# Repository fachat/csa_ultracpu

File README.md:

# Ultra-CPU

Note: this is a part of a larger set of repositories, with [upet_family](https://github.com/fachat/upet_family) as the main repository.

This is the CPU board for a re-incarnation of the Commodore PET or other computer(s) from the later 1970s.

It is build on a Eurocard board and has only parts that can still be obtained new in 2024.
It uses the [CS/A bus interface](http://www.6502.org/users/andre/csa/index.html) to use other I/O boards.

As the memory mapping is programmable using the FPGA on the board, multiple types of computers can
potentially re-created. I started with my favourite one, the Commodore PET.

The reason this board is called Ultra-CPU is because it can potentially be used to recreate not only the Commodore PET.
The downside compared to the Micro-PET is, that it needs a separate I/O board to re-create a Commodore PET.
This can be found [here on my CS/A page](http://www.6502.org/users/andre/csa/petio/index.html).

## Features

The board is built with a number of features:

- Commodore 3032 / 4032 / 8032 / 8296 with options menu to select at boot
  - Boot-menu to select different PET versions to run (BASIC 1, 2, 4)
  - 40 col character display
  - 80 col character display
- Improved system design:
  - 512k video RAM, plus 512k fast RAM, accessible using banks on the W65816 CPU
  - boot from an SPI Flash ROM
  - up to 17.5 MHz mode (via configuration register)
  - Write protection for the PET ROMs once copied to RAM
  - lower 32k RAM mappable from all of the 512k fast RAM
- Improved Video output:
  - VGA color video output (RGBI in 768x576 mode)
  - based on 720x576@60Hz VGA video timing (i.e. including borders at 40/80 columns)
  - modifyable character set
  - 40/80 column display switchable
  - 25/50 rows display switch
  - multiple video pages mappable to $8000 video mem address
  - Mulitple colour modes (Colour-PET, C128 VDC-compatible, Multicolour)
  - Colour Hires (VDC-compatible, Multicolour)
  - 16 colours out of a colour palette of 64 colours displayed simultaneously.
- DAC audio output
  - DMA engine to play audio samples on stereo sound output
- Built-in extra hardware:
  - USB host mode interface (for keyboard / mouse)
  - Real-Time-Clock (battery-buffered)
  - Ethernet/Wifi (via Breakout board)
  - SD-Card (via Breakout board)
- CS/A bus interface
  - multiple options to use bus devices, e.g. in I/O window
  - Together with [Ultra-Bus](https://github.com/fachat/csa_ultrabus) backplane Apple-II and RC2014 devices can be used

## Overview

The system architecture is actually rather simple, as you can see in the following graphics.

The main functionality is "hidden" inside the FPGA. It does:

1. clock generation and management
2. memory mapping
3. video generation.
4. SPI interface and boot

On the CPU side of the FPGA it is actually a rather almost normal 65816 computer, 
with the exception that the bank register (that catches and stores the address lines 
A16-23 from the CPU's data bus) is in the FPGA, and that there is no ROM. The ROM has been
replaced with some code in the FPGA that copies the initial program to the CPU accessible
RAM, taking it from the Flash Boot ROM via SPI. This actually simplifies the design,
as 

1. parallel ROMs are getting harder to come by and
2. they are typically not as fast as is needed, and
3. with the SPI boot they don't occupy valuable CPU address space.

The video generation is done using time-sharing access to the video RAM.
The VGA output is 720x576 at 50Hz. So there is a pixel clock of 27MHz.

The system runs at 13.5MHz, so a byte of pixel output (i.e. eight pixels) has four
memory accesses to VRAM. Two of them are reserved for video access, one for fetching the
character data (e.g. at $08xxx in the PET), and the second one to fetch the "character ROM"
data, i.e. the pixel data for a character. This is also stored in VRAM, and is being loaded
there from the Flash Boot ROM by the initial boot loader.

The FPGA reads the character data, stores it to fetch the character pixel data, and streams
that out using its internal video shift register.

For more detailled descriptions of the features and how to use them, pls see the 
[FPGA repository](https://github.com/fachat/upet_fpga),
as described in the next section.

## Version History

- [Revision 2.1A](https://github.com/fachat/csa_ultracpu/tree/r2.1a): Version using a Spartan 6 FPGA
- [Revision 1.3C](https://github.com/fachat/csa_ultracpu/tree/r1.3c): first working version using a Spartan 3E FPGA
- [Revision 1.2B](https://github.com/fachat/csa_ultracpu/tree/csa_ultracpu_1.2b): Version with CPLD and external colour generation.

## Known Issues

The following issues have been identified:

* Audio quality

Below are the fixes for these. Note, these are NOT yet in the BOM.

### Audio quality

The DAC audio output is not linear with the given schematics. This can be fixed by

* removing R30 and R32
* replace C3 and C10 with a 22uF  electrolytic cap. Orient minus pole to the output connector

## Building

Here are three subdirectories:

- [Board](Board/) That contains the board schematics and layout
- [Demo](Demo/) Some demo programs
- [tests](tests/) Some test programs

- [FPGA code](https://github.com/fachat/upet_fpga) This separate repository contains the VHDL code to program the FPGA logic chip used, and describes the configuration options - including the SPI and DAC usage and the Video feature and register description.
- [ROM](https://github.com/fachat/upet_roms) This separate repository contains the ROM contents to boot

### Board

To build the board, you have to find a provider that builds PCBs from Eagle .brd files.
Additionally, gerber files and a full Bill-of-material are provided in the Board subdirectory.

### FPGA

The FPGA is a Xilinx Spartan 6 programmable logic chip. It runs on 3.3V, 
so the bus interface has to convert between 3.3V and 5V. Compared to previous versions and the Micro-PET, also
the RAM and CPU on this board run on 3.3V now.
The FPGA logic here is programmed in VHDL.

The FPGA programming is actually stored in an SPI Flash Prom, so makes re-creating it even easier compared to 
the previous versions that used a CPLD - the CPLD required a separate programmer, now a (serial) Flash programmer suffices.

### ROM

The ROM image can be built using gcc, xa65, and make. Use your favourite EPROM programmer to burn it into the SPI Flash chip.

The ROM contains images of all required ROM images for BASIC 1, 2, and 4, and corresponding editor ROMs, including
some that have been extended with wedges and colour-PET functionality.

The updated editor ROMs are from [Steve's Editor ROM project](http://www.6502.org/users/sjgray/projects/editrom/index.html) and can handle C64 keyboards, has a DOS wedge included, and resets into the Micro-PET boot menu.

For more details see the [ROM repository](https://github.com/fachat/upet_roms)

## Gallery

### The system

### Graphics feature overview

Note that this version is without the (optional) "Brown Fix" that is included in version 1.0B of the board.

### Board

### Boot menu and OS boot screen

### V1.2 system views

### Debugging during development

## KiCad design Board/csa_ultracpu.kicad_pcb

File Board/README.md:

# Board

The board is a two-layer Eurocard, i.e. 160mm x 100mm.

## Schematics & Layout

The schematics and layout have been created with Cadsoft Eagle.
So, here you can find the 

- [csa_ultracpu.sch](csa_ultracpu.sch) and
- [csa_ultracpu.brd](csa_ultracpu.brd) files

But, you can still have a look at the schematics and layout using the
PNG images created

- [csa_ultracpu_v2.0b-sch-1.png](csa_ultracpu_v2.0b-sch-1.png) Part 1 - CS/A Bus interface
- [csa_ultracpu_v2.0b-sch-2.png](csa_ultracpu_v2.0b-sch-2.png) Part 2 - CPLD, CPU, Fast RAM
- [csa_ultracpu_v2.0b-sch-3.png](csa_ultracpu_v2.0b-sch-3.png) Part 3 - Power
- [csa_ultracpu_v2.0b-sch-4.png](csa_ultracpu_v2.0b-sch-4.png) Part 4 - Video and Audio output
- [csa_ultracpu_v2.0b-sch-5.png](csa_ultracpu_v2.0b-sch-5.png) Part 5 - SPI devices (Eth, USB, RTCC, ...)
- [csa_ultracpu_v2.0b-sch-6.png](csa_ultracpu_v2.0b-sch-6.png) Part 6 - Video RAM, data fetch and shift register

- [csa_ultracpu_v2.0b-layout.png](csa_ultracpu_v2.0b-layout.png) layout of the chips
- [csa_ultracpu_v2.0b-brd.png](csa_ultracpu_v2.0b-brd.png) layout of the traces

## Bill of Material

The main chips are:

- 1x W65816S CPU
- 1x x Spartan 6 FPGA
- 2x 8x512k parallel SRAM with 25ns access time
- Several ICs for Video generation
- several ICs for the bus interface
- 1x DS1813 RESET controller

- 70 MHZ crystal oscillator
- 16 MHZ crystal oscillator (bus clock - may be optional)

- Voltage regulators

- bypass caps

- 1x LM2937-3.3V SOT
- div. resistors/caps to generate 3.3V output

More details can be found in the [Eagle parts list](csa_ultracpu.csv).

A full [BOM](csa_ultracpu_BOM.xlsx) with parts numbers from Mouser is now provided as well.

## Changelog

### V2.0B

This moves from the Spartan 3 to a Spartan 6, increases clock speed to 70 MHz for a 
higher resolutoin video output, and more.

### V1.3C

This is a technology change of the programmable logic from the CPLD to an FPGA.
The FPGA has the same footprint, but much more space for logic inside. 
This allowed to integrate proper colour support, bitmaps, sprites, and many more
graphics features. A DAC allows outputting digital sound. 

### V1.0B

This fixes couple of things I found in V1.0A:

- The order of the color/intensity signals was the wrong way around
- The A/B and G inputs of IC15 had been accidently swapped
- An optional second color buffer has been removed as timing was good enough for it not be needed
- An optional "brown fix" has been added.
- On the board, two bypass caps were placed under the CPU socket
- On the board, the JP1 connector has been turned 180 degrees to confirm existing boards

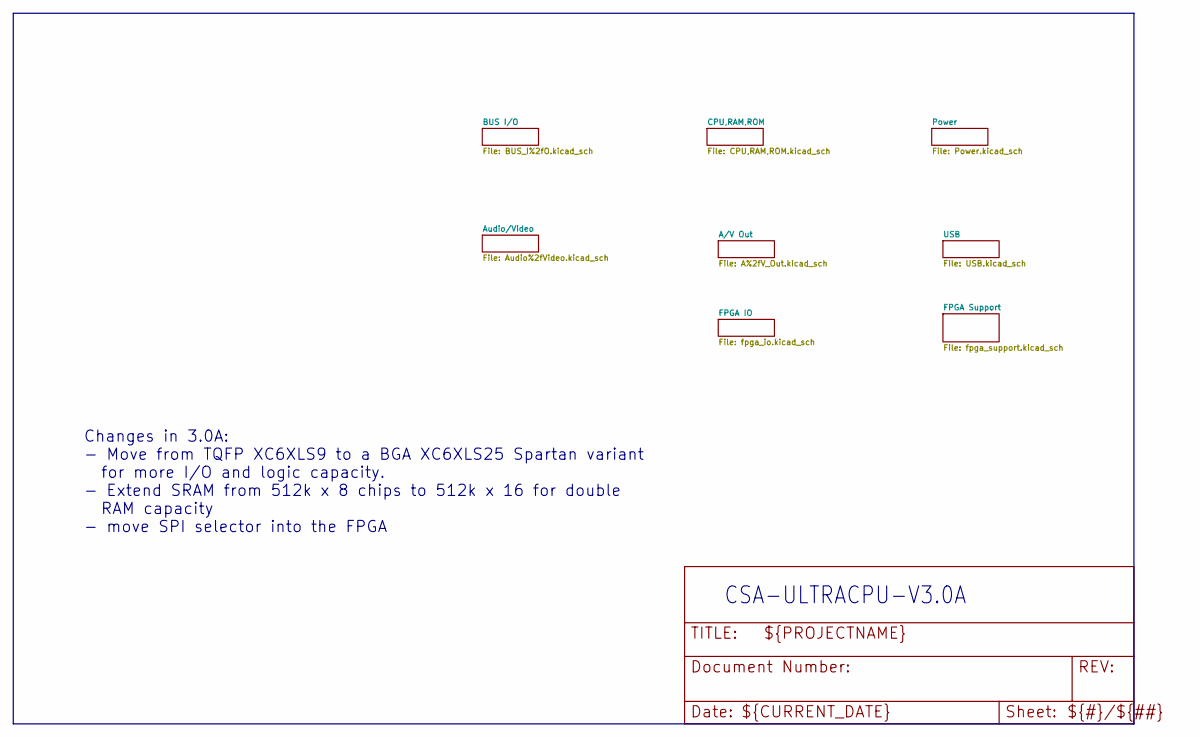
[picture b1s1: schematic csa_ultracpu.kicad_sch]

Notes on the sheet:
Changes in 3.0A: - Move from TQFP XC6XLS9 to a BGA XC6XLS25 Spartan variant for more I/O and logic capacity. - Extend SRAM from 512k x 8 chips to 512k x 16 for double RAM capacity - move SPI selector into the FPGA
CSA-ULTRACPU-V3.0A

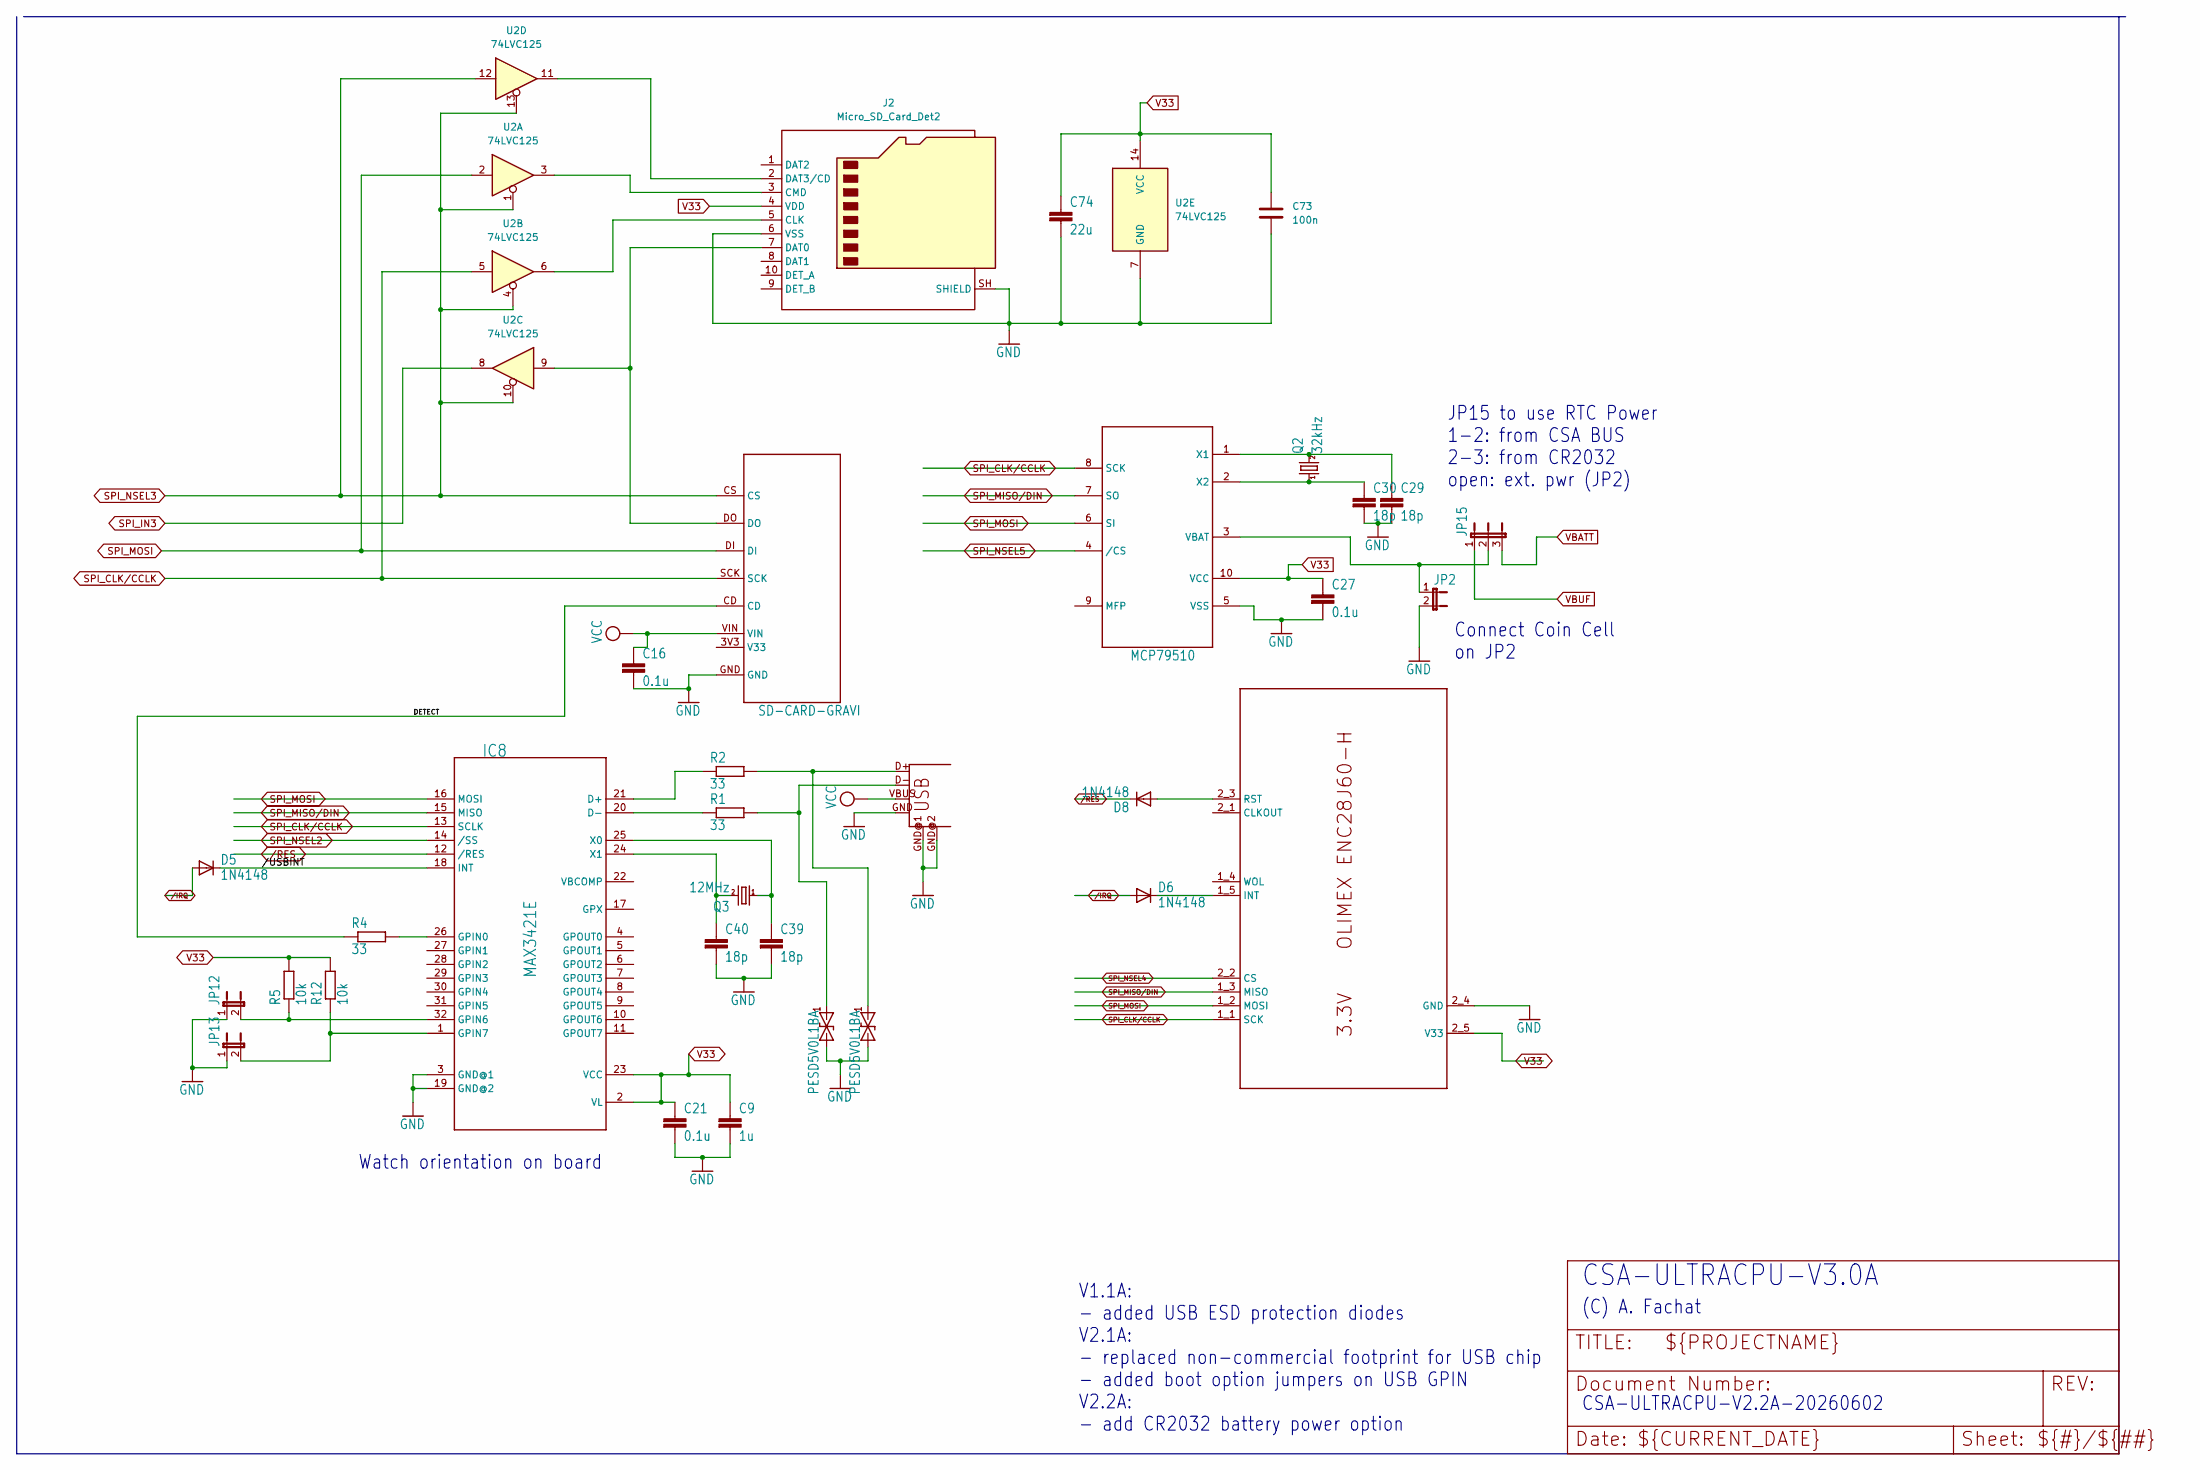
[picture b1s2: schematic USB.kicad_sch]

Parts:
C9: 1u; C0603; LCSC C15849
C16, C21, C27: 0.1u; C0603; LCSC C14663
C29, C30, C39, C40: 18p; C0603; LCSC C1647
C73: 100n; C_0603_1608Metric_Pad1.08x0.95mm_HandSolder; LCSC C14663
C74: 22u; C0805; LCSC C45783
D5, D6, D8: 1N4148; D-5; LCSC C402212
IC8: MAX3421E; VQFN-32-1EP_5x5mm_P0.5mm_EP3.15x3.15mm; LCSC C1870151
J2: Micro_SD_Card_Det2; microSD_HC_Molex_104031-0811; LCSC C585350
JP2, JP12, JP13: JP1E; JP1; LCSC C234182
JP15: JP2E; JP2; LCSC C587036
Q2: 32kHz; TC26H; LCSC C3013591
Q3: 12MHz; HC49_S; LCSC C16369
R1, R2, R4: 33; R_0805_2012Metric_Pad1.20x1.40mm_HandSolder; LCSC C17634
R5, R12: 10k; R_0805_2012Metric_Pad1.20x1.40mm_HandSolder; LCSC C17414
U2: 74LVC125; SO-14_3.9x8.65mm_P1.27mm; LCSC C6057
U$9: ETHOLIENC
U$12: SD-CARD-GRAVI; GRAVITECH-SDCARD; LCSC C27438
U$13: MCP79510; MSOP10; LCSC C627708
U$14, U$15: PESD5V0L1BA; SOD323; LCSC C2687118
USB1: USB-A-H; LCSC C456018

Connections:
/USB/DETECT: R4.1, U$12.CD
/USB//USBINT: D5.C, IC8.18 (INT)
GND: C9.2, C16.2, C21.2, C27.2, C29.2, C30.2, C39.2, C40.2, C73.2, C74.2, IC8.3 (GND@1), IC8.19 (GND@2), J2.6 (VSS), J2.SH (SHIELD), JP2.2, JP12.1, JP13.1, U2.7 (GND), U$9.2_4 (GND), U$12.GND, U$13.5 (VSS), U$14.1 (2), U$15.1 (2), USB1.GND, USB1.GND@1, USB1.GND@2; also elsewhere on the board
unnamed: IC8.21 (D+), R2.1
unnamed: IC8.20 (D-), R1.1
unnamed: IC8.26 (GPIN0), R4.2
unnamed: IC8.32 (GPIN6), JP12.2, R5.1
unnamed: IC8.1 (GPIN7), JP13.2, R12.1
unnamed: C39.1, IC8.25 (X0), Q3.1
unnamed: C40.1, IC8.24 (X1), Q3.2
unnamed: J2.5 (CLK), U2.6
unnamed: J2.3 (CMD), U2.3
unnamed: J2.7 (DAT0), U2.9, U$12.DO
unnamed: J2.2 (DAT3/CD), U2.11
unnamed: D6.C, U$9.1_5 (INT)
unnamed: D8.A, U$9.2_3 (RST)
unnamed: JP2.1, JP15.2, U$13.3 (VBAT)
unnamed: C29.1, Q2.2, U$13.1 (X1)
unnamed: C30.1, Q2.1, U$13.2 (X2)
unnamed: R2.2, U$14.2 (1), USB1.D+
unnamed: R1.2, U$15.2 (1), USB1.D-
SPI_CLK/CCLK: IC8.13 (SCLK), U2.5, U$9.1_1 (SCK), U$12.SCK, U$13.8 (SCK); also elsewhere on the board
SPI_IN3: U2.8; also elsewhere on the board
SPI_MISO/DIN: IC8.15 (MISO), U$9.1_3 (MISO), U$13.7 (SO); also elsewhere on the board
SPI_MOSI: IC8.16 (MOSI), U2.2, U$9.1_2 (MOSI), U$12.DI, U$13.6 (SI); also elsewhere on the board
SPI_NSEL2: IC8.14 (/SS); also elsewhere on the board
SPI_NSEL3: U2.1, U2.4, U2.10, U2.12, U2.13, U$12.CS; also elsewhere on the board
SPI_NSEL4: U$9.2_2 (CS); also elsewhere on the board
SPI_NSEL5: U$13.4 (/CS); also elsewhere on the board
V33: C9.1, C21.1, C27.1, C73.1, C74.1, IC8.2 (VL), IC8.23 (VCC), J2.4 (VDD), R5.2, R12.2, U2.14 (VCC), U$9.2_5 (V33), U$13.10 (VCC); also elsewhere on the board
VBATT: JP15.3; also elsewhere on the board
VBUF: JP15.1; also elsewhere on the board
VCC: C16.1, U$12.VIN, USB1.VBUS; also elsewhere on the board
/IRQ: D5.A, D6.A; also elsewhere on the board
/RES: D8.C, IC8.12 (/RES); also elsewhere on the board

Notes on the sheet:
CSA-ULTRACPU-V3.0A
V1.1A: - added USB ESD protection diodes V2.1A: - replaced non-commercial footprint for USB chip - added boot option jumpers on USB GPIN V2.2A: - add CR2032 battery power option
CSA-ULTRACPU-V2.2A-20260602
(C) A. Fachat
Connect Coin Cell on JP2
Watch orientation on board~{}
JP15 to use RTC Power 1-2: from CSA BUS 2-3: from CR2032 open: ext. pwr (JP2)

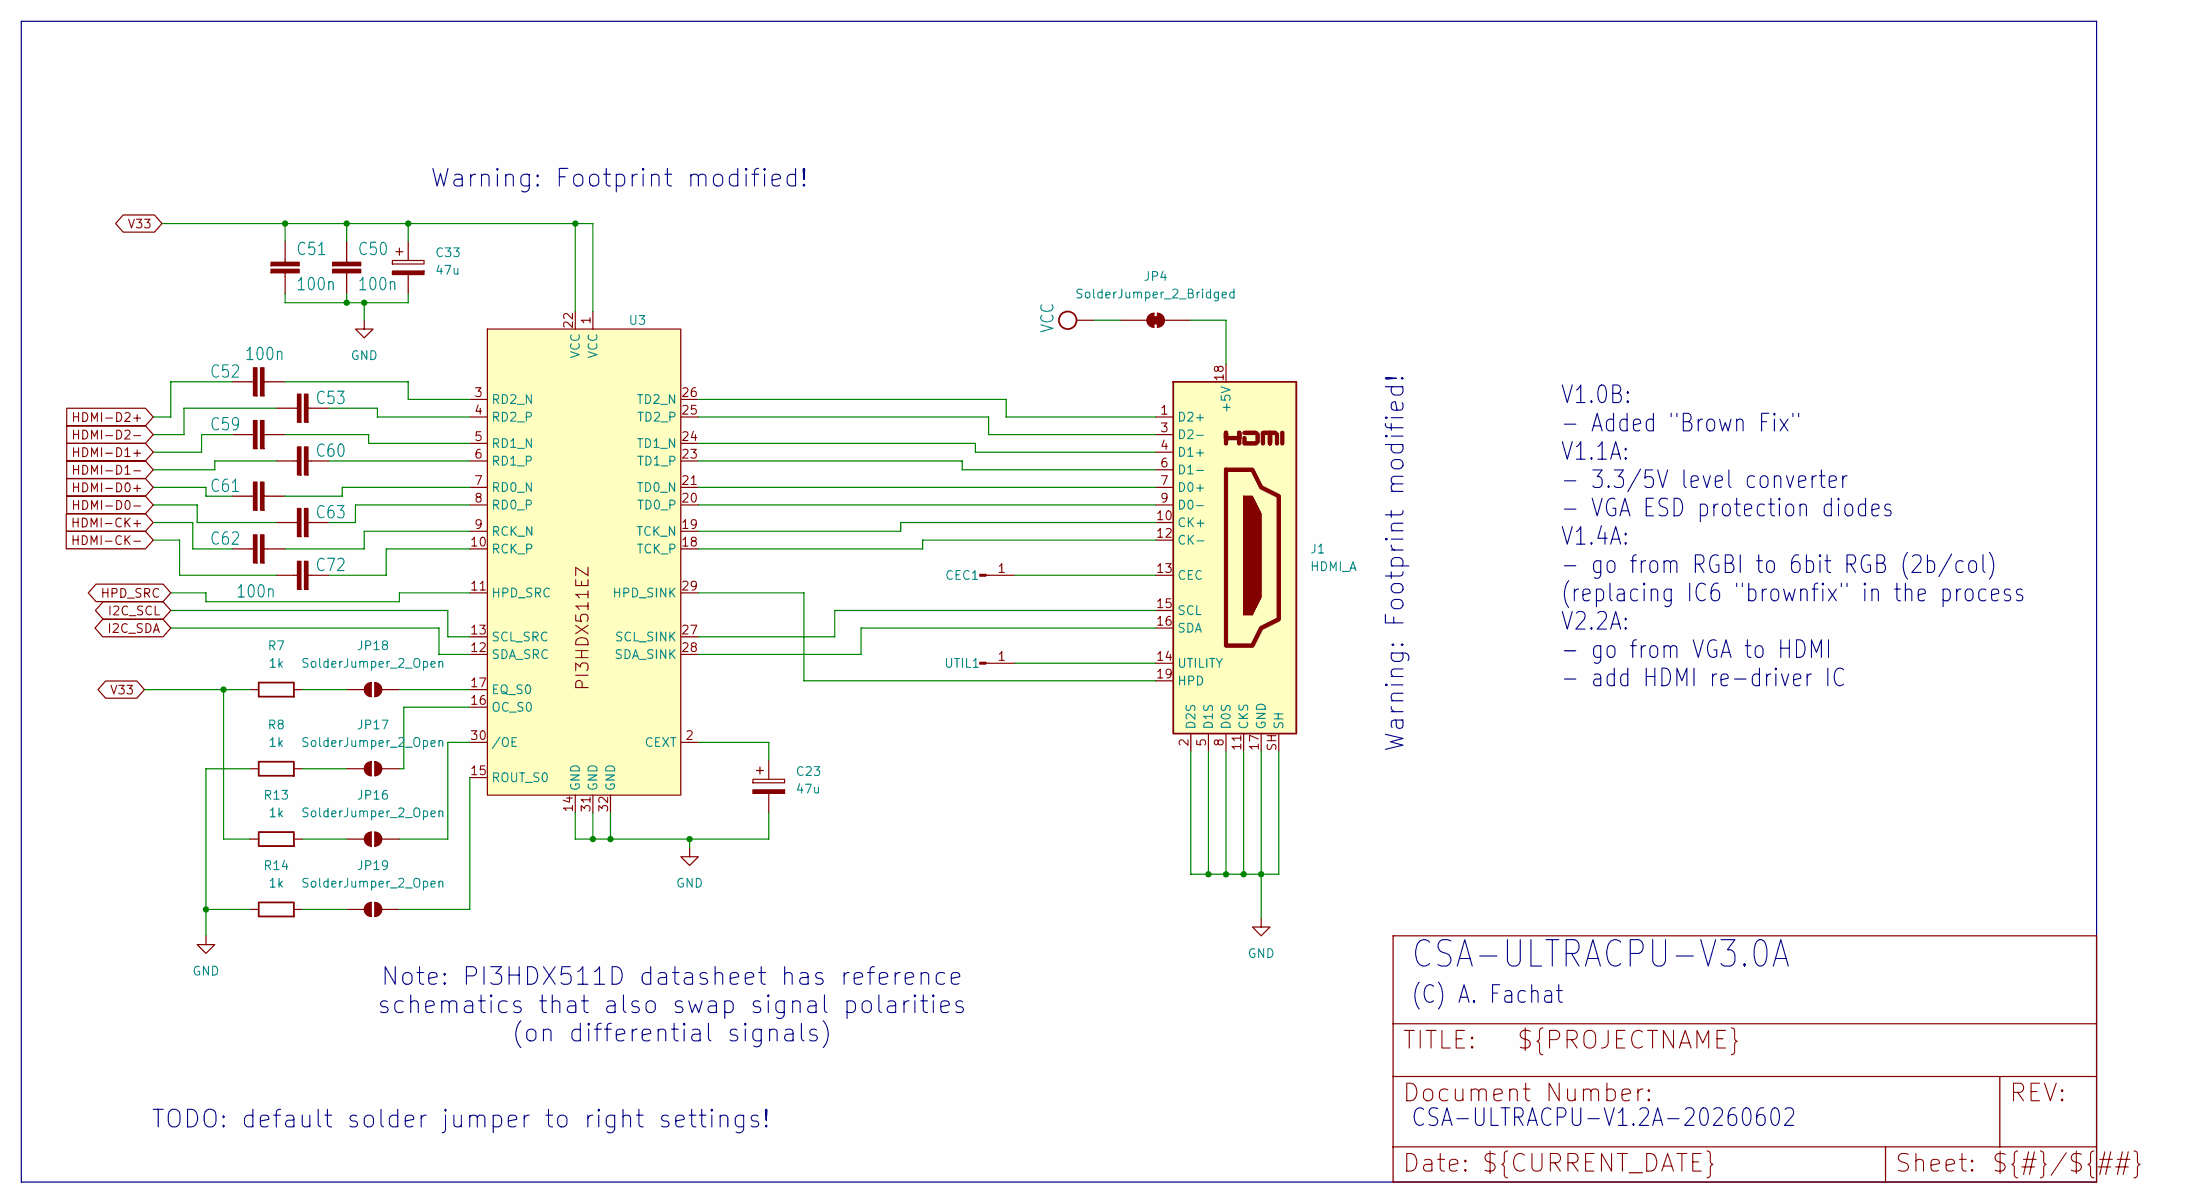
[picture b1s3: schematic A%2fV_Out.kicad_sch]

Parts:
C23, C33: 47u; C_0805_2012Metric_Pad1.18x1.45mm_HandSolder; LCSC C16780
C50, C51, C52, C53, C59, C60, C61, C62, C63, C72: 100n; C_0603_1608Metric_Pad1.08x0.95mm_HandSolder; LCSC C14663
CEC1: Conn_01x01_Pin; PinHeader_1x01_P1.00mm_Vertical
J1: HDMI_A; HDMI_A_Molex_208658-1001_Horizontal; LCSC C138388
JP4: SolderJumper_2_Bridged; SolderJumper-2_P1.3mm_Bridged_RoundedPad1.0x1.5mm
JP16, JP17, JP18, JP19: SolderJumper_2_Open; SolderJumper-2_P1.3mm_Open_RoundedPad1.0x1.5mm
R7, R8, R13, R14: 1k; R_0603_1608Metric_Pad0.98x0.95mm_HandSolder; LCSC C21190
U3: Diodes_ZL32_TQFN-32-1EP_3x6mm_P0.4mm_EP1.25x3.5mm; LCSC C2674182
UTIL1: Conn_01x01_Pin; PinHeader_1x01_P1.00mm_Vertical

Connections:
GND: C23.2, C33.2, C50.2, C51.2, J1.2 (D2S), J1.5 (D1S), J1.8 (D0S), J1.11 (CKS), J1.17 (GND), J1.SH, R8.1, R14.1, U3.14 (GND), U3.31 (GND), U3.32 (GND); also elsewhere on the board
HDMI-CK+: C62.1; also elsewhere on the board
HDMI-CK-: C72.1; also elsewhere on the board
HDMI-D0+: C61.1; also elsewhere on the board
HDMI-D0-: C63.1; also elsewhere on the board
HDMI-D1+: C59.1; also elsewhere on the board
HDMI-D1-: C60.1; also elsewhere on the board
HDMI-D2+: C52.1; also elsewhere on the board
HDMI-D2-: C53.1; also elsewhere on the board
HPD_SRC: U3.11 (HPD_SRC); also elsewhere on the board
I2C_SCL: U3.13 (SCL_SRC); also elsewhere on the board
I2C_SDA: U3.12 (SDA_SRC); also elsewhere on the board
unnamed: CEC1.1 (Pin_1_1), J1.13 (CEC)
unnamed: J1.18 (+5V), JP4.2 (B)
unnamed: J1.10 (CK+), U3.19 (TCK_N)
unnamed: J1.12 (CK-), U3.18 (TCK_P)
unnamed: J1.7 (D0+), U3.21 (TD0_N)
unnamed: J1.9 (D0-), U3.20 (TD0_P)
unnamed: J1.4 (D1+), U3.24 (TD1_N)
unnamed: J1.6 (D1-), U3.23 (TD1_P)
unnamed: J1.1 (D2+), U3.26 (TD2_N)
unnamed: J1.3 (D2-), U3.25 (TD2_P)
unnamed: J1.19 (HPD), U3.29 (HPD_SINK)
unnamed: J1.15 (SCL), U3.27 (SCL_SINK)
unnamed: J1.16 (SDA), U3.28 (SDA_SINK)
unnamed: J1.14 (UTILITY), UTIL1.1 (Pin_1_1)
unnamed: JP16.1 (A), R13.2
unnamed: JP16.2 (B), U3.30 (/OE)
unnamed: JP17.1 (A), R8.2
unnamed: JP17.2 (B), U3.16 (OC_S0)
unnamed: JP18.1 (A), R7.2
unnamed: JP18.2 (B), U3.17 (EQ_S0)
unnamed: JP19.1 (A), R14.2
unnamed: JP19.2 (B), U3.15 (ROUT_S0)
unnamed: C23.1, U3.2 (CEXT)
unnamed: C62.2, U3.9 (RCK_N)
unnamed: C72.2, U3.10 (RCK_P)
unnamed: C61.2, U3.7 (RD0_N)
unnamed: C63.2, U3.8 (RD0_P)
unnamed: C59.2, U3.5 (RD1_N)
unnamed: C60.2, U3.6 (RD1_P)
unnamed: C52.2, U3.3 (RD2_N)
unnamed: C53.2, U3.4 (RD2_P)
V33: C33.1, C50.1, C51.1, R7.1, R13.1, U3.1 (VCC), U3.22 (VCC); also elsewhere on the board
VCC: JP4.1 (A); also elsewhere on the board

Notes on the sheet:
Warning: Footprint modified!
(C) A. Fachat
CSA-ULTRACPU-V1.2A-20260602
Note: PI3HDX511D datasheet has reference schematics that also swap signal polarities (on differential signals)
V1.0B: - Added "Brown Fix" V1.1A: - 3.3/5V level converter - VGA ESD protection diodes V1.4A: - go from RGBI to 6bit RGB (2b/col) (replacing IC6 "brownfix" in the process V2.2A: - go from VGA to HDMI - add HDMI re-driver IC
CSA-ULTRACPU-V3.0A
TODO: default solder jumper to right settings!

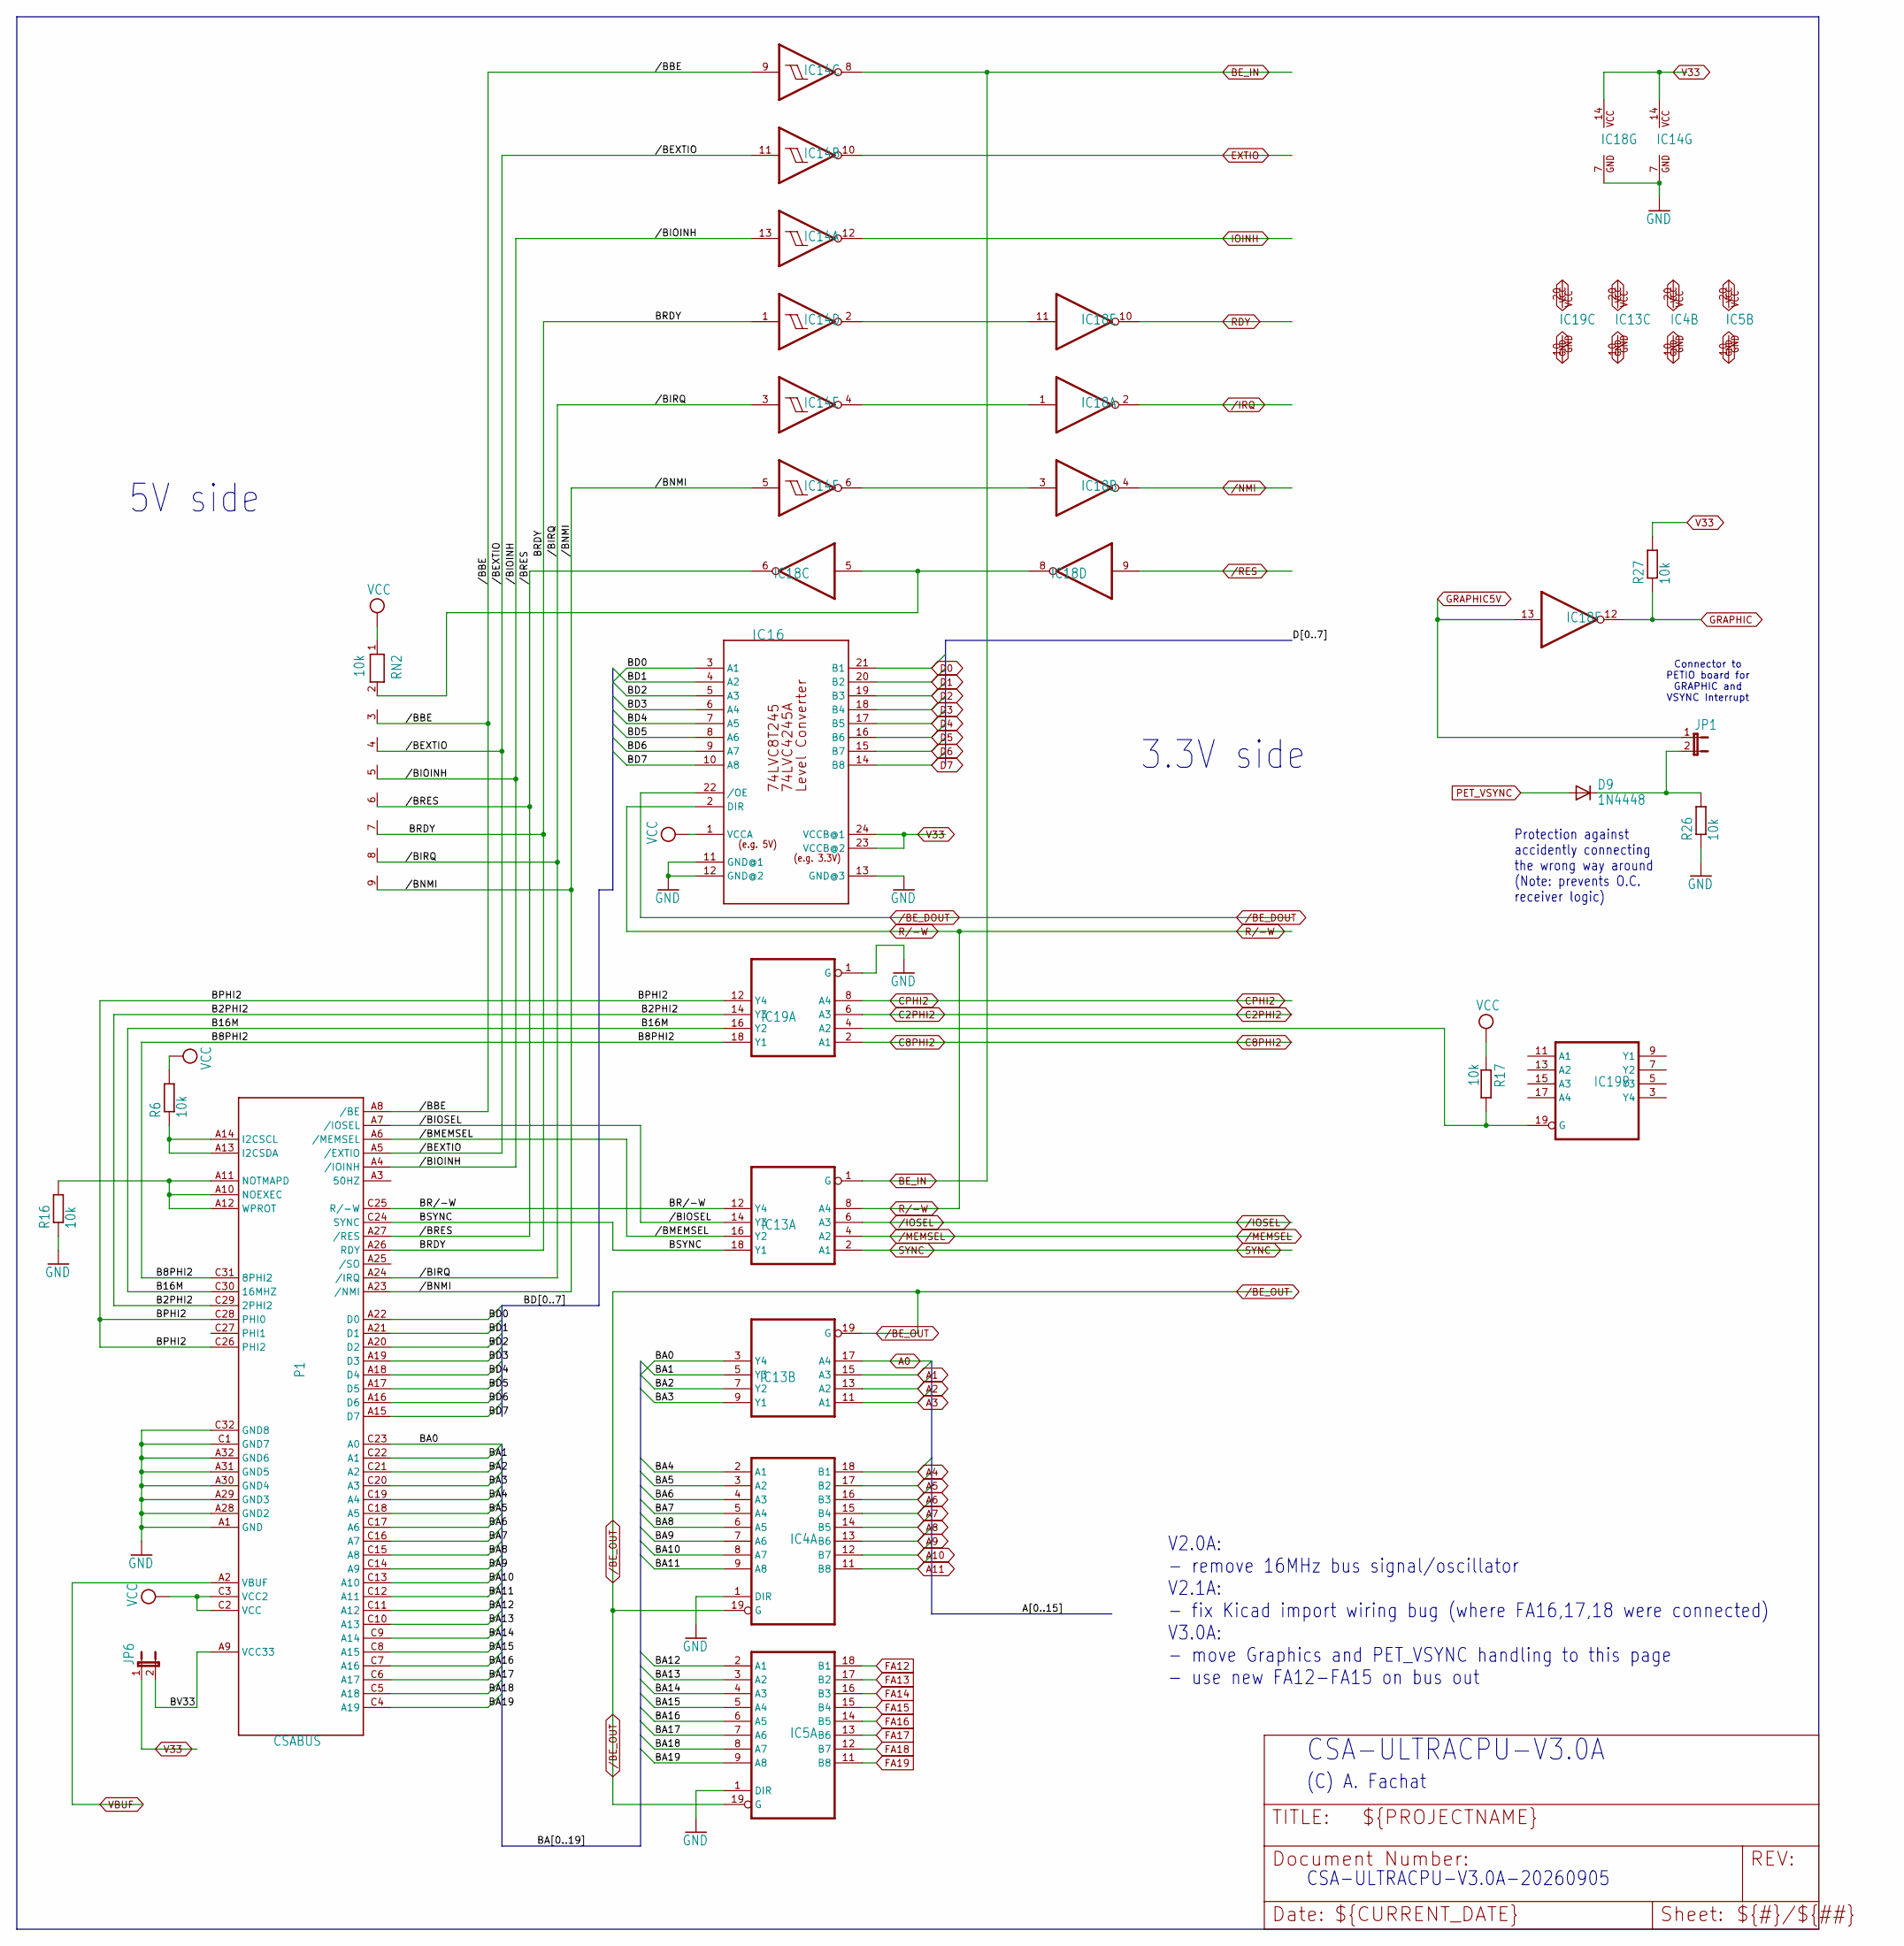
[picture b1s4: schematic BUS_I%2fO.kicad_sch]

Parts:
D9: 1N4448; D_SOD-123; LCSC C81598
IC4, IC5: 74HCT245DW; SO20W; LCSC C132267
IC13, IC19: 74244DW; SO20W; LCSC C6776
IC14: 74LVC14; SO14; LCSC C133541
IC16: 74LVC8T245SO24; SO24L; LCSC C2677625
IC18: 74LVC06; SO14; LCSC C7658
JP1: JP1E; PinHeader_1x02_P2.54mm_Horizontal; LCSC C54570432
JP6: JP1E; JP1; LCSC C234182
P1: CSABUS; LCSC C5173362
R6, R16, R17, R26, R27: 10k; R_0805_2012Metric_Pad1.20x1.40mm_HandSolder; LCSC C17414
RN2: 10k; RN-9; LCSC C8692

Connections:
/BUS I/O/B2PHI2: IC19.14 (Y3), P1.C29 (2PHI2)
/BUS I/O/B8PHI2: IC19.18 (Y1), P1.C31 (8PHI2)
/BUS I/O/B16M: IC19.16 (Y2), P1.C30 (16MHZ)
/BUS I/O/BA0: IC13.3 (Y4), P1.C23 (A0)
/BUS I/O/BA1: IC13.5 (Y3), P1.C22 (A1)
/BUS I/O/BA2: IC13.7 (Y2), P1.C21 (A2)
/BUS I/O/BA3: IC13.9 (Y1), P1.C20 (A3)
/BUS I/O/BA4: IC4.2 (A1), P1.C19 (A4)
/BUS I/O/BA5: IC4.3 (A2), P1.C18 (A5)
/BUS I/O/BA6: IC4.4 (A3), P1.C17 (A6)
/BUS I/O/BA7: IC4.5 (A4), P1.C16 (A7)
/BUS I/O/BA8: IC4.6 (A5), P1.C15 (A8)
/BUS I/O/BA9: IC4.7 (A6), P1.C14 (A9)
/BUS I/O/BA10: IC4.8 (A7), P1.C13 (A10)
/BUS I/O/BA11: IC4.9 (A8), P1.C12 (A11)
/BUS I/O/BA12: IC5.2 (A1), P1.C11 (A12)
/BUS I/O/BA13: IC5.3 (A2), P1.C10 (A13)
/BUS I/O/BA14: IC5.4 (A3), P1.C9 (A14)
/BUS I/O/BA15: IC5.5 (A4), P1.C8 (A15)
/BUS I/O/BA16: IC5.6 (A5), P1.C7 (A16)
/BUS I/O/BA17: IC5.7 (A6), P1.C6 (A17)
/BUS I/O/BA18: IC5.8 (A7), P1.C5 (A18)
/BUS I/O/BA19: IC5.9 (A8), P1.C4 (A19)
/BUS I/O/BD0: IC16.3 (A1), P1.A22 (D0)
/BUS I/O/BD1: IC16.4 (A2), P1.A21 (D1)
/BUS I/O/BD2: IC16.5 (A3), P1.A20 (D2)
/BUS I/O/BD3: IC16.6 (A4), P1.A19 (D3)
/BUS I/O/BD4: IC16.7 (A5), P1.A18 (D4)
/BUS I/O/BD5: IC16.8 (A6), P1.A17 (D5)
/BUS I/O/BD6: IC16.9 (A7), P1.A16 (D6)
/BUS I/O/BD7: IC16.10 (A8), P1.A15 (D7)
/BUS I/O/BPHI2: IC19.12 (Y4), P1.C26 (PHI2), P1.C28 (PHI0)
/BUS I/O/BRDY: IC14.1 (I), P1.A26 (RDY), RN2.7
/BUS I/O/BR/-W: IC13.12 (Y4), P1.C25 (R/-W)
/BUS I/O/BSYNC: IC13.18 (Y1), P1.C24 (SYNC)
/BUS I/O/BV33: JP6.2, P1.A9 (VCC33)
/BUS I/O//BBE: IC14.9 (I), P1.A8 (/BE), RN2.3
/BUS I/O//BEXTIO: IC14.11 (I), P1.A5 (/EXTIO), RN2.4
/BUS I/O//BIOINH: IC14.13 (I), P1.A4 (/IOINH), RN2.5
/BUS I/O//BIOSEL: IC13.14 (Y3), P1.A7 (/IOSEL)
/BUS I/O//BIRQ: IC14.3 (I), P1.A24 (/IRQ), RN2.8
/BUS I/O//BMEMSEL: IC13.16 (Y2), P1.A6 (/MEMSEL)
/BUS I/O//BNMI: IC14.5 (I), P1.A23 (/NMI), RN2.9
/BUS I/O//BRES: IC18.6 (O), P1.A27 (/RES), RN2.6
A0: IC13.17 (A4); also elsewhere on the board
A1: IC13.15 (A3); also elsewhere on the board
A2: IC13.13 (A2); also elsewhere on the board
A3: IC13.11 (A1); also elsewhere on the board
A4: IC4.18 (B1); also elsewhere on the board
A5: IC4.17 (B2); also elsewhere on the board
A6: IC4.16 (B3); also elsewhere on the board
A7: IC4.15 (B4); also elsewhere on the board
A8: IC4.14 (B5); also elsewhere on the board
A9: IC4.13 (B6); also elsewhere on the board
A10: IC4.12 (B7); also elsewhere on the board
A11: IC4.11 (B8); also elsewhere on the board
BE_IN: IC13.1 (G), IC14.8 (O); also elsewhere on the board
C2PHI2: IC19.6 (A3); also elsewhere on the board
C8PHI2: IC19.2 (A1); also elsewhere on the board
CPHI2: IC19.8 (A4); also elsewhere on the board
D0: IC16.21 (B1); also elsewhere on the board
D1: IC16.20 (B2); also elsewhere on the board
D2: IC16.19 (B3); also elsewhere on the board
D3: IC16.18 (B4); also elsewhere on the board
D4: IC16.17 (B5); also elsewhere on the board
D5: IC16.16 (B6); also elsewhere on the board
D6: IC16.15 (B7); also elsewhere on the board
D7: IC16.14 (B8); also elsewhere on the board
EXTIO: IC14.10 (O); also elsewhere on the board
FA12: IC5.18 (B1); also elsewhere on the board
FA13: IC5.17 (B2); also elsewhere on the board
FA14: IC5.16 (B3); also elsewhere on the board
FA15: IC5.15 (B4); also elsewhere on the board
FA16: IC5.14 (B5); also elsewhere on the board
FA17: IC5.13 (B6); also elsewhere on the board
FA18: IC5.12 (B7); also elsewhere on the board
FA19: IC5.11 (B8); also elsewhere on the board
GND: IC4.1 (DIR), IC4.10 (GND), IC5.1 (DIR), IC5.10 (GND), IC13.10 (GND), IC14.7 (GND), IC16.11 (GND@1), IC16.12 (GND@2), IC16.13 (GND@3), IC18.7 (GND), IC19.1 (G), IC19.10 (GND), P1.A1 (GND), P1.A28 (GND2), P1.A29 (GND3), P1.A30 (GND4), P1.A31 (GND5), P1.A32 (GND6), P1.C1 (GND7), P1.C32 (GND8), R16.1, R26.1; also elsewhere on the board
GRAPHIC: IC18.12 (O), R27.1; also elsewhere on the board
GRAPHIC5V: IC18.13 (I), JP1.1
IOINH: IC14.12 (O); also elsewhere on the board
unnamed: D9.1 (C), JP1.2, R26.2
unnamed: IC14.2 (O), IC18.11 (I)
unnamed: IC14.4 (O), IC18.1 (I)
unnamed: IC14.6 (O), IC18.3 (I)
unnamed: IC18.5 (I), IC18.8 (O), RN2.2
unnamed: IC19.4 (A2), IC19.19 (G), R17.2
unnamed: P1.A13 (I2CSDA), P1.A14 (I2CSCL), R6.1
unnamed: P1.A10 (NOEXEC), P1.A11 (NOTMAPD), P1.A12 (WPROT), R16.2
PET_VSYNC: D9.2 (A); also elsewhere on the board
RDY: IC18.10 (O); also elsewhere on the board
SYNC: IC13.2 (A1); also elsewhere on the board
V33: IC14.14 (VCC), IC16.23 (VCCB@2), IC16.24 (VCCB@1), IC18.14 (VCC), JP6.1, R27.2; also elsewhere on the board
VBUF: P1.A2 (VBUF); also elsewhere on the board
VCC: IC4.20 (VCC), IC5.20 (VCC), IC13.20 (VCC), IC16.1 (VCCA), IC19.20 (VCC), P1.C2 (VCC), P1.C3 (VCC2), R6.2, R17.1, RN2.1; also elsewhere on the board
/BE_DOUT: IC16.22 (/OE); also elsewhere on the board
/BE_OUT: IC4.19 (G), IC5.19 (G), IC13.19 (G); also elsewhere on the board
/IOSEL: IC13.6 (A3); also elsewhere on the board
/IRQ: IC18.2 (O); also elsewhere on the board
/MEMSEL: IC13.4 (A2); also elsewhere on the board
/RES: IC18.9 (I); also elsewhere on the board

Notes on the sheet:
5V side
Connector to PETIO board for GRAPHIC and VSYNC Interrupt
V2.0A: - remove 16MHz bus signal/oscillator V2.1A: - fix Kicad import wiring bug (where FA16,17,18 were connected) V3.0A: - move Graphics and PET_VSYNC handling to this page - use new FA12-FA15 on bus out
CSA-ULTRACPU-V3.0A
(C) A. Fachat
3.3V side
CSA-ULTRACPU-V3.0A-20260905
Protection against accidently connecting the wrong way around (Note: prevents O.C. receiver logic)

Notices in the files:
Board/csa_ultracpu.kicad_pcb:
(C) 2026
(C) 2021,2026
